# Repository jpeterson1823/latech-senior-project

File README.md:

# P.R.I.S.M. Local Home Assistant Platform

Gotta set this up soon...

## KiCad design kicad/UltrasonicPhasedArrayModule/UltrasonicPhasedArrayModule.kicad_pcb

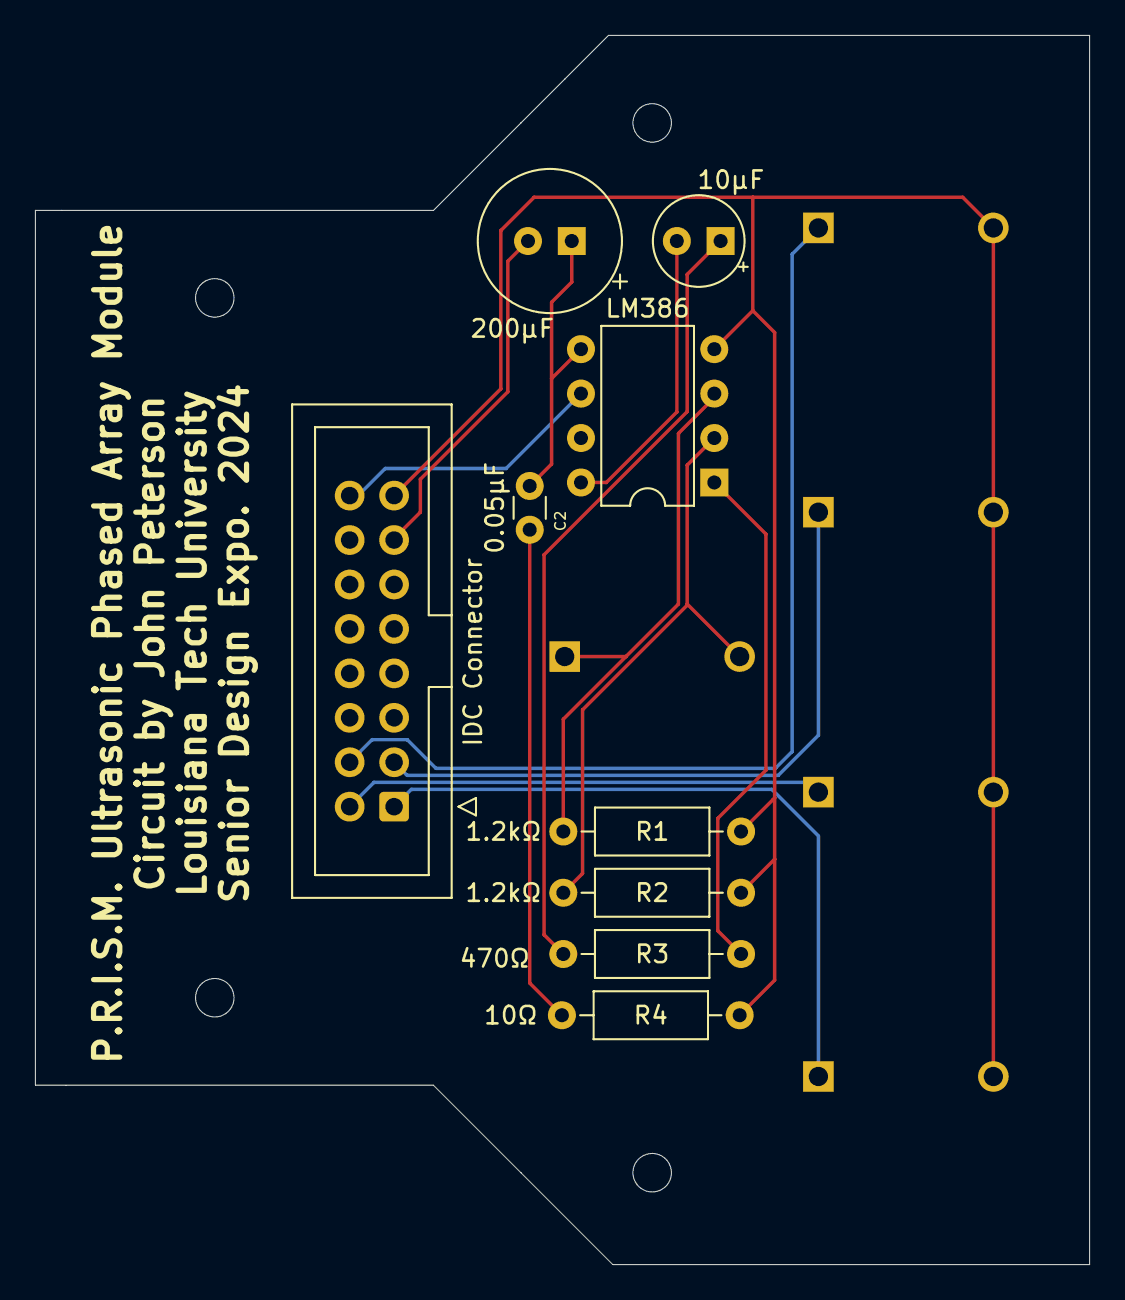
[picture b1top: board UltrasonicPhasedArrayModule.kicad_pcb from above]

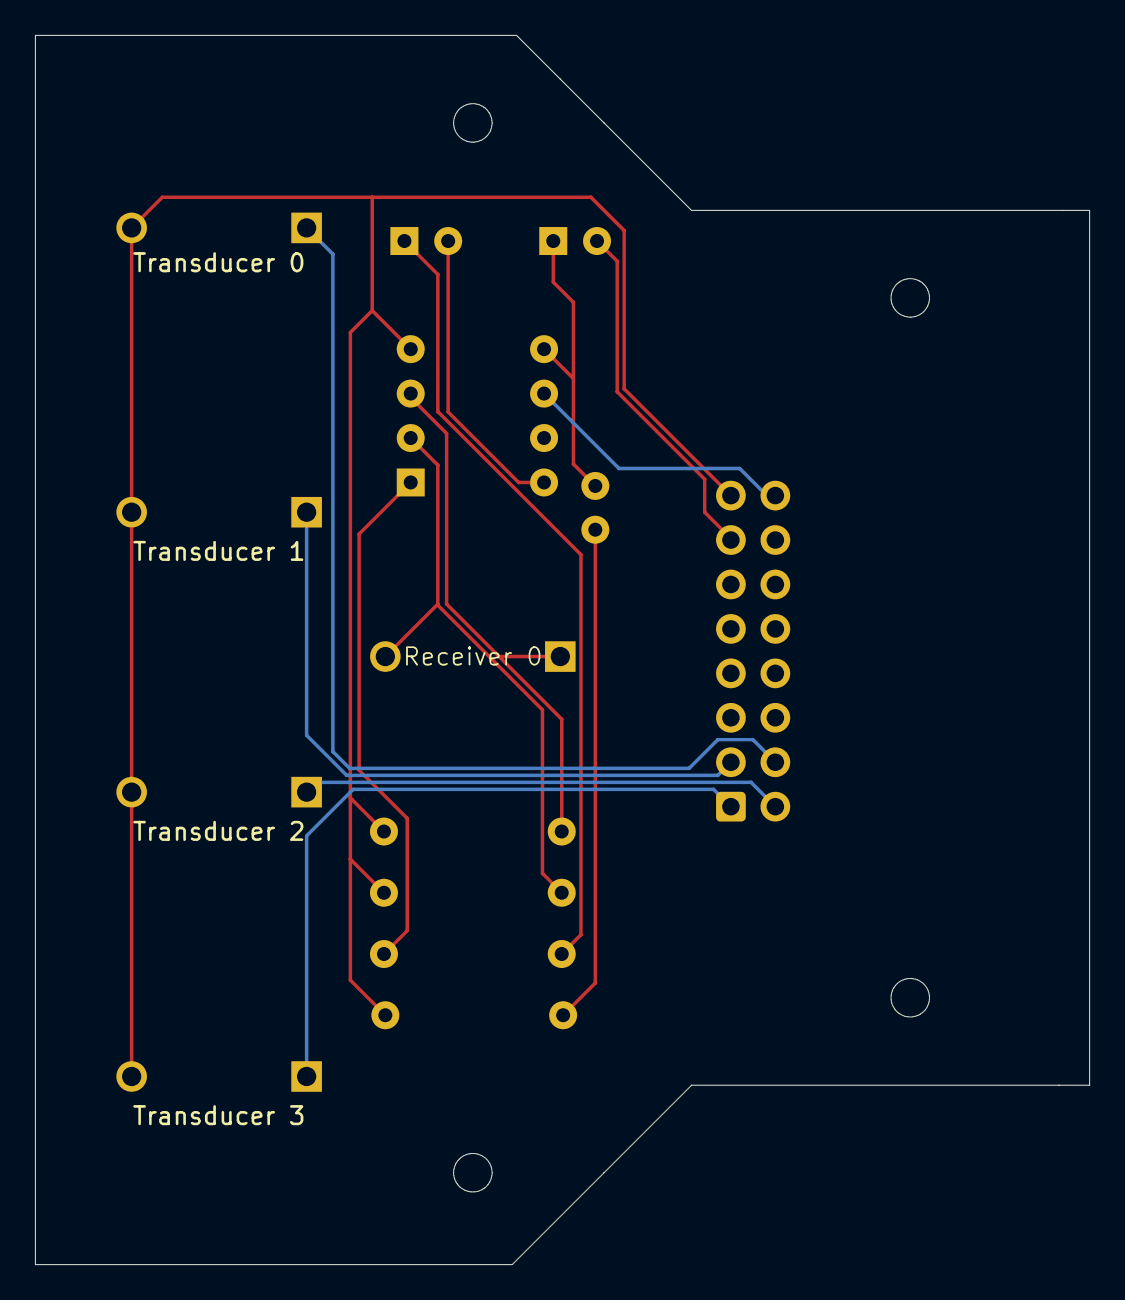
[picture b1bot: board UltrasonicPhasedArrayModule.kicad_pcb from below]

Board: 2 copper layers, 60.2 x 70.2 mm, 14 parts (5 on the bottom side), 14 nets.

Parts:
C1: 200μF; CP_Radial_Tantal_D8.0mm_P2.50mm
C2: 0.05μF; C_Disc_D3.0mm_W1.6mm_P2.50mm
C3: 10μF; CP_Radial_Tantal_D5.0mm_P2.50mm
J1: IDC Connector; IDC-Header_2x08_P2.54mm_Vertical
LS1: Transducer 3; Ultrasonic Transducer-Receiver
LS2: Transducer 2; Ultrasonic Transducer-Receiver
LS3: Transducer 1; Ultrasonic Transducer-Receiver
LS4: Transducer 0; Ultrasonic Transducer-Receiver
R1, R2: 1.2kΩ; R_Axial_DIN0207_L6.3mm_D2.5mm_P10.16mm_Horizontal
R3: 470Ω; R_Axial_DIN0207_L6.3mm_D2.5mm_P10.16mm_Horizontal
R4: 10Ω; R_Axial_DIN0207_L6.3mm_D2.5mm_P10.16mm_Horizontal
Receiver 0: Microphone_Ultrasound; Ultrasonic Transducer-Receiver
U1: LM386; DIP-8_W7.62mm

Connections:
/GND: J1.15, LS1.2, LS2.2, LS3.2, LS4.2, R1.2, R2.1, R4.1, U1.4 (GND)
/Vsys: J1.16, U1.6 (V+)
unnamed: C1.1, C2.1, U1.5
unnamed: C2.2, R4.2
unnamed: C3.1, R3.1
unnamed: C3.2, U1.8 (GAIN)
unnamed: J1.1, LS1.1
unnamed: J1.2, LS2.1
unnamed: J1.3, LS3.1
unnamed: J1.4, LS4.1
unnamed: C1.2, J1.13
unnamed: R2.2, Receiver 0.2 (+), U1.2 (-)
unnamed: R1.1, Receiver 0.1 (-), U1.3 (+)
unnamed: R3.2, U1.1 (GAIN)

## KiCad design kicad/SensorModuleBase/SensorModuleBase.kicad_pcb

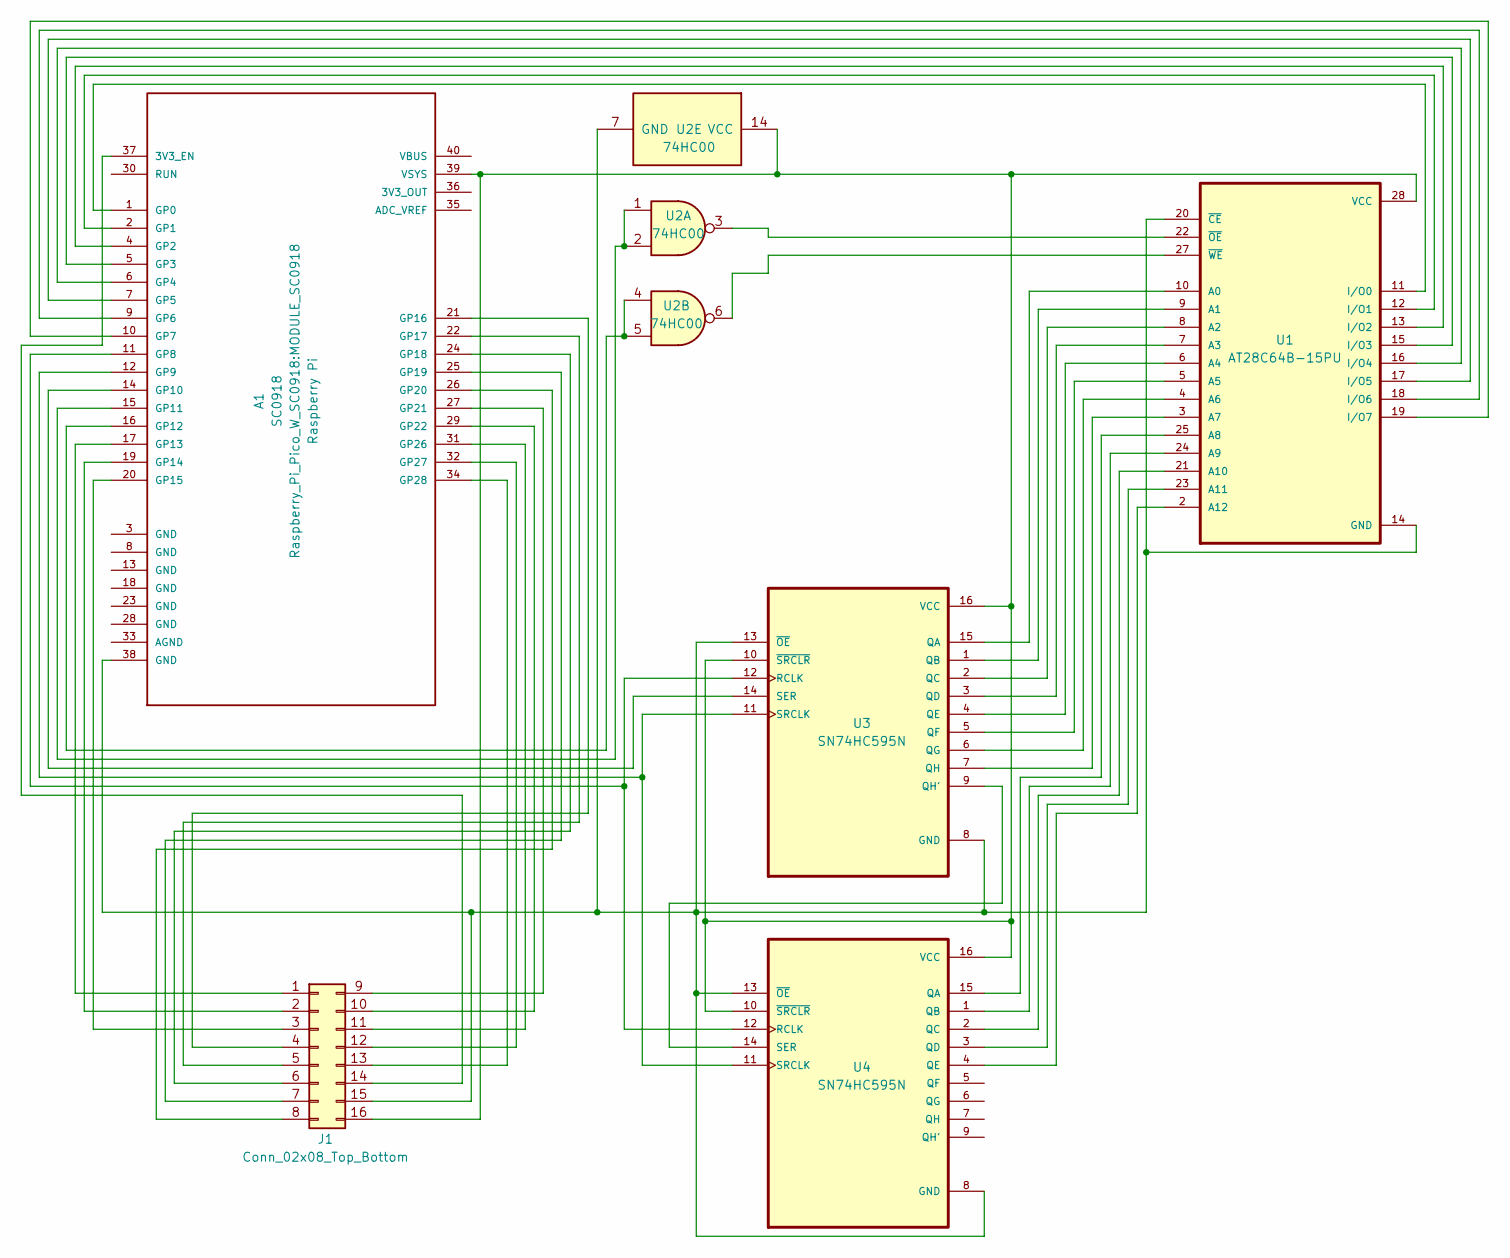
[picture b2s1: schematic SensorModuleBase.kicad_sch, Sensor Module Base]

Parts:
A1: SC0918; MODULE_SC0918; PARTREV 1.6
J1: Conn_02x08_Top_Bottom; IDC-Header_2x08_P2.54mm_Vertical
U1: AT28C64B-15PU; DIP1555W45P254L3733H482Q28; PARTREV B
U2: 74HC00; DIP-14_W7.62mm
U3, U4: SN74HC595N; DIP794W45P254L1969H508Q16; DigiKey_Part_Number 296-1600-5-ND

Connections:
unnamed: A1.37 (3V3_EN), J1.14
unnamed: A1.1 (GP0), U1.11 (I/O0)
unnamed: A1.2 (GP1), U1.12 (I/O1)
unnamed: A1.4 (GP2), U1.13 (I/O2)
unnamed: A1.5 (GP3), U1.15 (I/O3)
unnamed: A1.6 (GP4), U1.16 (I/O4)
unnamed: A1.7 (GP5), U1.17 (I/O5)
unnamed: A1.9 (GP6), U1.18 (I/O6)
unnamed: A1.10 (GP7), U1.19 (I/O7)
unnamed: A1.11 (GP8), U3.12 (RCLK), U4.12 (RCLK)
unnamed: A1.12 (GP9), U3.11 (SRCLK), U4.11 (SRCLK)
unnamed: A1.14 (GP10), U3.14 (SER)
unnamed: A1.15 (GP11), U2.1, U2.2
unnamed: A1.16 (GP12), U2.4, U2.5
unnamed: A1.17 (GP13), J1.1
unnamed: A1.19 (GP14), J1.2
unnamed: A1.20 (GP15), J1.3
unnamed: A1.21 (GP16), J1.4
unnamed: A1.22 (GP17), J1.5
unnamed: A1.24 (GP18), J1.6
unnamed: A1.25 (GP19), J1.7
unnamed: A1.26 (GP20), J1.8
unnamed: A1.27 (GP21), J1.9
unnamed: A1.29 (GP22), J1.10
unnamed: A1.31 (GP26), J1.11
unnamed: A1.32 (GP27), J1.12
unnamed: A1.34 (GP28), J1.13
unnamed: A1.39 (VSYS), J1.16, U1.28 (VCC), U2.14 (VCC), U3.10 (~SRCLR), U3.16 (VCC), U4.10 (~SRCLR), U4.16 (VCC)
unnamed: A1.38 (GND), J1.15, U1.14 (GND), U1.20 (~CE), U2.7 (GND), U3.8 (GND), U3.13 (~OE), U4.8 (GND), U4.13 (~OE)
unnamed: U1.10 (A0), U3.15 (QA)
unnamed: U1.9 (A1), U3.1 (QB)
unnamed: U1.8 (A2), U3.2 (QC)
unnamed: U1.7 (A3), U3.3 (QD)
unnamed: U1.6 (A4), U3.4 (QE)
unnamed: U1.5 (A5), U3.5 (QF)
unnamed: U1.4 (A6), U3.6 (QG)
unnamed: U1.3 (A7), U3.7 (QH)
unnamed: U1.25 (A8), U4.15 (QA)
unnamed: U1.24 (A9), U4.1 (QB)
unnamed: U1.21 (A10), U4.2 (QC)
unnamed: U1.23 (A11), U4.3 (QD)
unnamed: U1.2 (A12), U4.4 (QE)
unnamed: U1.22 (~OE), U2.3
unnamed: U1.27 (~WE), U2.6
unnamed: U3.9 (QH'), U4.14 (SER)

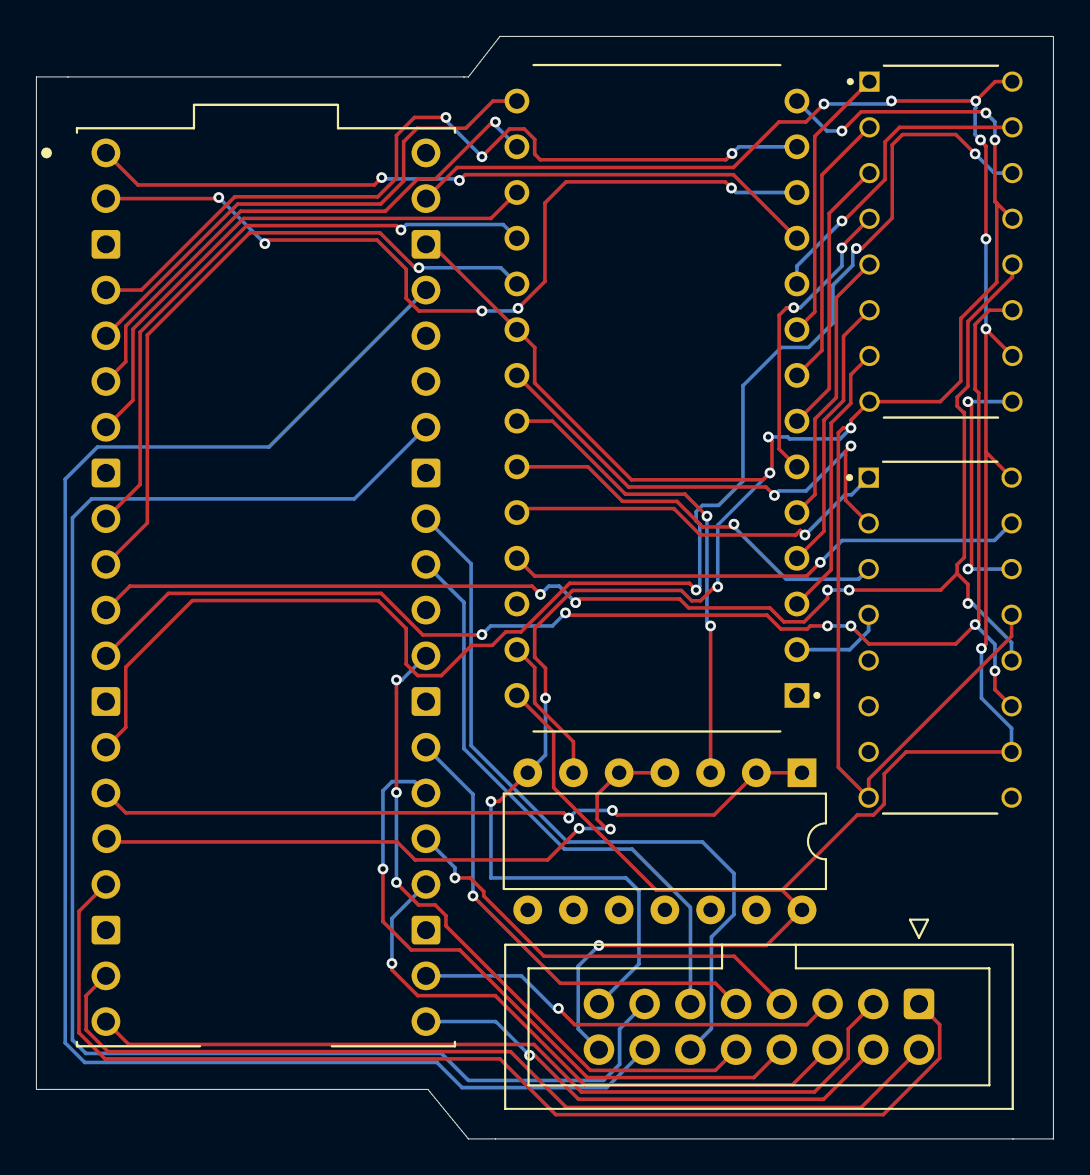
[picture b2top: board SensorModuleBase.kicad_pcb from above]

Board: 2 copper layers, 56.5 x 61.2 mm, 6 parts (0 on the bottom side), 45 nets.

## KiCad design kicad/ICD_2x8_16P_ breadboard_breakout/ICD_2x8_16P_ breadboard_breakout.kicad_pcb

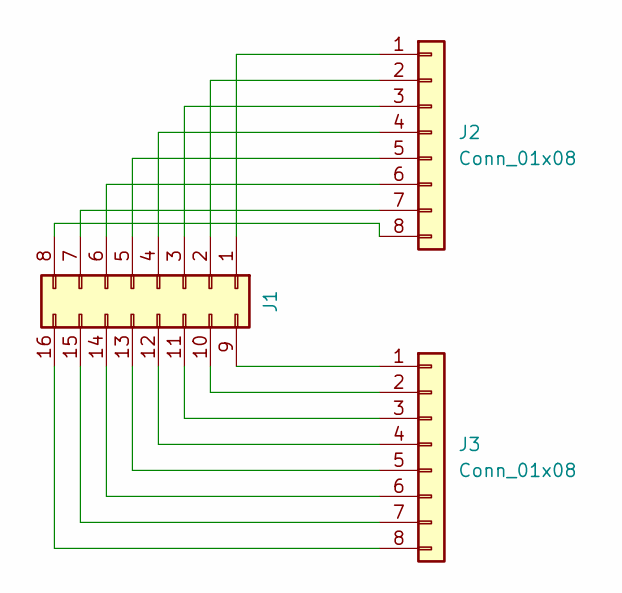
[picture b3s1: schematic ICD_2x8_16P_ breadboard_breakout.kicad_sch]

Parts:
J1: Conn_02x08_Top_Bottom; IDC-Header_2x08_P2.54mm_Vertical
J2, J3: Conn_01x08; PinHeader_1x08_P2.54mm_Vertical

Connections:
unnamed: J1.1, J2.1
unnamed: J1.2, J2.2
unnamed: J1.3, J2.3
unnamed: J1.4, J2.4
unnamed: J1.5, J2.5
unnamed: J1.6, J2.6
unnamed: J1.7, J2.7
unnamed: J1.8, J2.8
unnamed: J1.9, J3.1
unnamed: J1.10, J3.2
unnamed: J1.11, J3.3
unnamed: J1.12, J3.4
unnamed: J1.13, J3.5
unnamed: J1.14, J3.6
unnamed: J1.15, J3.7
unnamed: J1.16, J3.8

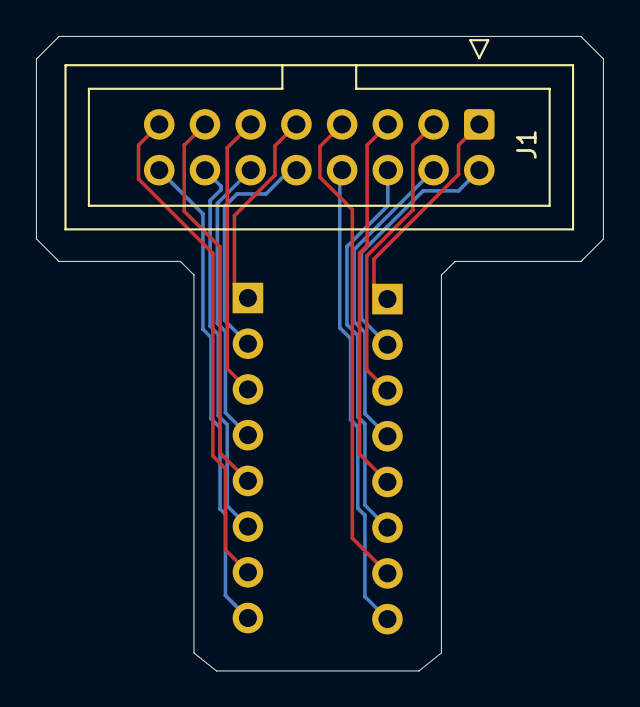
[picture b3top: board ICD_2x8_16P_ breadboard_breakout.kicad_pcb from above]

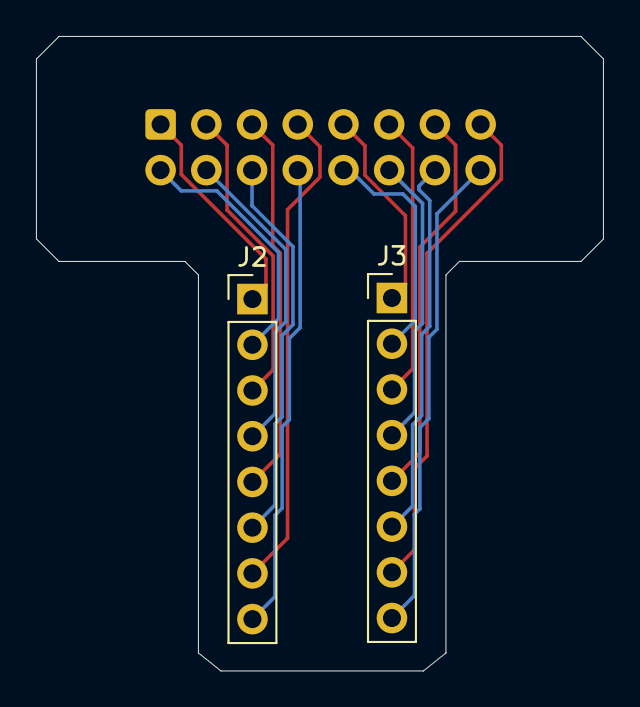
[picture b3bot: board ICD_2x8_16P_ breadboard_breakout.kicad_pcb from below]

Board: 2 copper layers, 31.5 x 35.2 mm, 3 parts (2 on the bottom side), 16 nets.

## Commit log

2024-01-10 initializing branch and commiting webdev progress so far
2024-01-16 Updated README, added apache, mysql, docker, and docker hub
    This is a large commit. In it I: updated the readme file, setup docker containers connected via docker compose, saved the docker images to docker hub for sharing, and added php for functionality betw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
2024-01-19 Creating sensor module branch and uploading current progress
2024-01-20 TCP/HTTP proof of concept code commit
2024-01-21 Network, Hardware, and TCP Socket Improvements
    Added redundancies to the WiFi connect function and restructured the
    Setup and Connect methods.
    Added GPIO setup for a tactile button.
    Restructured project file hierarchy.
2024-01-22 Started the Socket Implementation
    Fixed make issues for Windows and created HPP skeleton of SocketTCP class.
2024-01-23 Test tcp socket code refactored into proper class: SocketTCP
2024-01-29 Started work on Uplink class.
2024-02-13 Uploading progress
2024-02-13 Creation of Kantoku and completed SerialSetup
2024-02-15 Finished SerialSetup and started work on network pairing
2024-02-15 Added API's via PHP functionality and a Webpage for our prototype
2024-02-16 Modified Docker & Web/Database Environment for Hardware Testing for Demo Day/Prototyping
2024-02-16 Updating Git Branch
2024-02-20 Added linux python3 venv and added HttpReq class.
2024-02-20 Started work on NeoSocket, a better version of the current socket implementation.
2024-02-20 updating api functionality to work with hardware
2024-02-20 Finished NeoSocket and have proof of concept finished
2024-02-20 Updated gitignore
2024-02-20 Merge and removal of testing stuff from main.
    Merged with sensor-modules branch as proof-of-concept code is finished.
2024-02-20 Updated for Demo Day
2024-02-21 Got rid of pages
    the pages are unnecessary for this
2024-02-21 Got rid of Dockerfile
    it is unnecessary for this repo
2024-03-18 Added KiCAD Files and started work on UPA sensor
2024-03-21 added some kicad files and fixed circuit
2024-03-21 Updated some of the KiCAD files and started on UPA sensor module code.
2024-03-25 fixed routing issue in second.html
    When I moved second.html into pages/ for organization, some of the referrence paths used for the hyperlinks were changed. Considering using full paths or better referrence paths to prevent this from 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
2024-03-27 Pushing slight updates and progress on UPA
2024-03-28 Continuing work on UPA sensor. Started on Sweeping poll code.
2024-04-02 SensorModule: Major Progress SensorModule py3 library for DHCP leasing and management completed. SensorModule C/C++ source code for UPA sensor module is complete; testing is needed and accuracy tunin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
2024-04-08 Initial Main + Calendar Push
    Main Window and Calendar Window
2024-04-08 Major progress on Serial, KiCAD models, and Python libraries for sensor module base.
2024-04-08 Removing python vertual environment files
2024-04-10 Newly Implemented Designs
    Implemented and updated a new mysql design. The database design has been tested but still requires further testing. I also started adding/updated files to implement a login/signup feature for the web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
2024-04-11 More progress on SerialSession and pairing. Removed deprecated code.
2024-04-14 Updated Login Forms & CSS
2024-04-14 Added venv
2024-04-15 14hr Training
2024-04-16 Working Model
2024-04-16 Updated Main Folder with Weather and Calendar
    Pair function still needed.
2024-04-16 API Key Delete
2024-04-17 Slightly better model
2024-04-18 Reincluded bin folder
2024-04-19 Finished new Sensor Base KiCAD module and working on serial pairing.
    Serial pairing issue: deadlock between cores due to core1 failing to read data from std::cin.
2024-04-19 Started work on UPA OP-AMP Circuit
2024-04-19 Added missing 10oh resistor on output of LM386
2024-04-21 Shifted to one model for each speaker instead of one for all
2024-04-23 Successful models and voice recording script
2024-04-23 KiCAD Files Completed and General UPA Update
    KiCAD design files for the base module and UPA module are completed and on order.
    The UPA sensor code is now fully operational. One issue: accuracy of the beam forming. A recalculation of delay timing is required. EEPROM does not seem to write/read properly on breadboard, though t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
    KNOWN ISSUES:
    * UPA beam forming not accurate
    * EEPROM fails to read/write properly.
2024-04-23 Added storing prcessed data functionality
2024-04-23 Change for Voice Commands
    Worked on integration with John W. This is the updated code.
2024-04-23 Updated weather app to integrate with John W
2024-04-23 Continuing work on serial session. Will need to convert to non-multicore option.
2024-04-24 forgot the users folder
2024-04-24 adding processed audio data
2024-04-24 minor changes
2024-04-24 Mysterious Issue with PySerial
    Serial comms works when manually sent via VSCode's serial monitor, but magically explodes when using PySerial. Pico fails to IDENT, then begins looping \x23\x12\x00\x00\x0a for some reason. The bytes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
2024-04-24 Serial Comms Finished; Port of Python Library to C++
    PySerial is garbage and I cannot get it to work. I'm sure I just missed something, but serial communication using my custom packet library worked immediately when using CPP in place of Python3 for ho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
2024-04-25 Added Lucas's files to start integration
2024-04-25 This main contains code to work with Clay's DB
    It is not fully functional and working. Still need to do more work on this.
2024-04-25 Update main.ui with wthrBtn and userBtn
2024-04-25 continuing work on cpp port of py lib
2024-04-25 DHCPMan and Serial work. DHCPMan forking and lease aquisition code completed: testing needed. Serial and Pairing namespaces and functions created.
2024-04-25 Restoring Files, Improving Website Functionality, & Integration for GUI
    I messed up on a git pull and had to restore some files. Also, this commit includes new files that works towards integration with the gui side of our project.
2024-04-26 Password Hashing, Failed Signup Redirect, & Reflected changes of Updated Database
2024-04-26 Updated main.py
    Since our database uses MySQL and its python library has similar syntax to SQLLite3, which was being used here prviously, I swapped it out. There was few changes in syntax, so everything should work 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
2024-04-26 Updated Docker Image of Apache Server
2024-04-27 Small additions for GUI integration with Voice model
2024-04-27 Updated gui_main.py with code that Integrates the database
    Just added the code to integrate our database with gui_main.py's code 👍.
2024-04-27 Updating Progress
2024-04-27 Another API Key Delete
2024-04-27 Made progress on sensor
2024-04-28 Serial pairing code complete. Working on network update for sensor base.
2024-04-28 Started work on alerting and Kantoku's main loop.
2024-04-28 Started work on Sensor Listening library. Needs testing.
2024-04-28 Removing VSCode's odd settings
2024-04-30 Finished pairing fork to dbLeaseLoader script and completed dbLeaseLoader.
2024-04-30 Continuing work on pairing.
2024-04-30 Updated CSS & PHP Functionality
2024-04-30 Updated Database Queries
2024-04-30 Organized branch into proper python project and updated functionality to work with current version of other components of PRISM.
2024-04-30 Implemented some further updates for interfacing with db.
2024-04-30 Started implementation with DB and GUI.
2024-05-01 Started on pairing code
2024-05-01 Merging
2024-05-01 Cleaning up main branch
2024-05-01 Initializing this branch.
2024-05-01 Added some Web Functionality & Configured Apache Server
2024-05-01 Updated Necessary Files For Product Deployment
2024-05-02 Synchronization of recording and parsing
2024-05-02 Update gitignore
2024-05-02 Recieving and Parsing commands complete
2024-05-02 Wacky eeprom cleaner no workie, but upload.
2024-05-02 Fixed docker-compose.yml File
    accidentally deleted one line of code (specifying the database server's ports) in the docker-compose.yml file
2024-05-02 General progress.
2024-05-02 Further progress on GUI-Sensor Pairing implementation. TODO: - Save and load IPv4 settings on PICO instead of using hard-coded IP. - Make GUI Pairing interface a bit more well-rounded. FINISHED: - Pa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
2024-05-02 forgot to bring a model over for testing
2024-05-02 missing files
2024-05-02 testing
2024-05-03 updated apache image with proxy.php
2024-05-03 GUI and recording can happen at the same time
2024-05-03 Server backend and Sensor Module implemented successfully.
2024-05-03 Still need to make events
2024-05-03 Implemented sensor listening thread. MAIN now opens a listening thread and queue handler for all sensor HTTP Post request sent to the http.server instance.
    TODO:
    - Default user for Calander.py
    - Control currently visible app via sensor polling
    - Control currently visible app via voice command
2024-05-03 Voice commands activate calendar and weather windows
2024-05-04 worked on a more modular php script for dealing with hardware http requests
    essentially created a new file called api.php which processes desired functionality via an expected json input
2024-05-06 Added Pair functionality, sped up parsing
2024-05-06 Working Setup for Demo
2024-05-06 Completed a basic EEPROM tool
    Added eeprom-tool executable and created basic code for reading, writing, and decyphering formatted EEPROMS and displaying output to Serial Console.
2024-05-06 Removed odd files and added basic README
2024-05-06 Updated Web Server's Api.php script
2024-05-07 Forked process for audio processing
2024-05-07 brought Lucas's audio over, forgot to grab his model
2024-05-07 working
2024-05-08 Module able to destinguish between users
2024-05-08 Temporarily adding apache conf file
    This is for temporary development purposes
2024-05-08 UPA Sensor Tuning completed. Analysis Visual code completed.
2024-05-09 Finalizing some tuning adjustments to the UPA pingSweep method.
2024-05-09 JohnP's model added
2024-05-09 fixed merge issues
2024-05-09 still keying on mic
2024-05-09 did some testing
2024-05-09 no changes
2024-05-09 Removed Speaker Verification
2024-05-09 Finishing stufsf
2024-05-09 Working Demo
